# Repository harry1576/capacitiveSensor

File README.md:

# Capacitive Moisture Sensor
A sensor used to detect the present soil moisture through a change in capacitance. 
The PCB has designed in KiCad and uses an interdigital capacitor design.
The output signal from this board is a PWM with frequency that changes
relative to the capacitance (soil moisture).

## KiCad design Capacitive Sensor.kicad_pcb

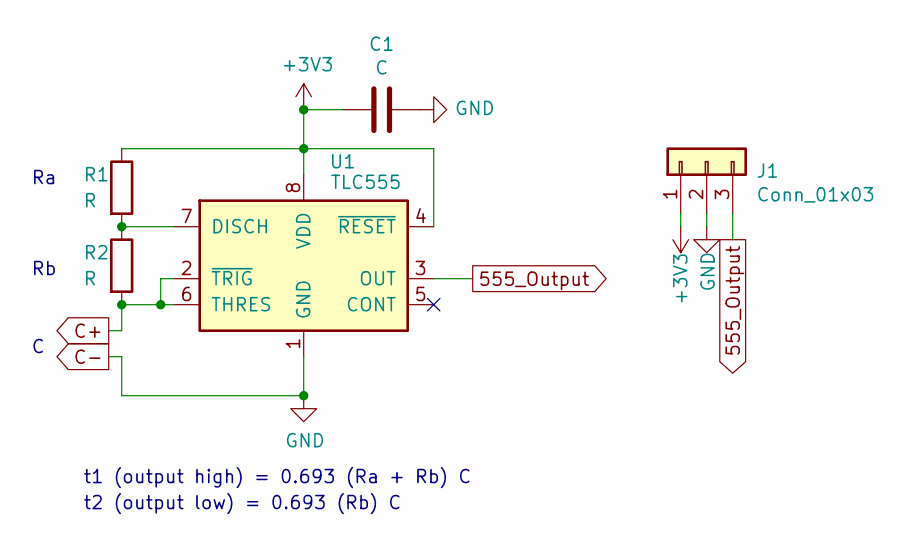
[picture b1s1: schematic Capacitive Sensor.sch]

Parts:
C1: C; C_0603_1608Metric
J1: Conn_01x03; Molex_CLIK-Mate_502386-0370_1x03-1MP_P1.25mm_Horizontal
R1, R2: R; R_0603_1608Metric
U1: TLC555; SOIC-8-1EP_3.9x4.9mm_P1.27mm_EP2.29x3mm

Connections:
555_Output: J1.3, U1.3 (OUT)
+3V3: C1.1, J1.1, R1.1, U1.4 (~RESET), U1.8 (VDD)
C+: R2.2, U1.2 (~TRIG), U1.6 (THRES)
C-: C1.2, J1.2, U1.1 (GND)
unnamed: R1.2, R2.1, U1.7 (DISCH)

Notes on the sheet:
t1 (output high) = 0.693 (Ra + Rb) C
t2 (output low) = 0.693 (Rb) C

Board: 2 copper layers, 5 parts (0 on the bottom side), 5 nets, no tracks yet.

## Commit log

2020-11-09 Inital commit
2020-11-10 update sensor
2021-06-04 tidied up repo and improved readme
2021-06-04 reame fix
